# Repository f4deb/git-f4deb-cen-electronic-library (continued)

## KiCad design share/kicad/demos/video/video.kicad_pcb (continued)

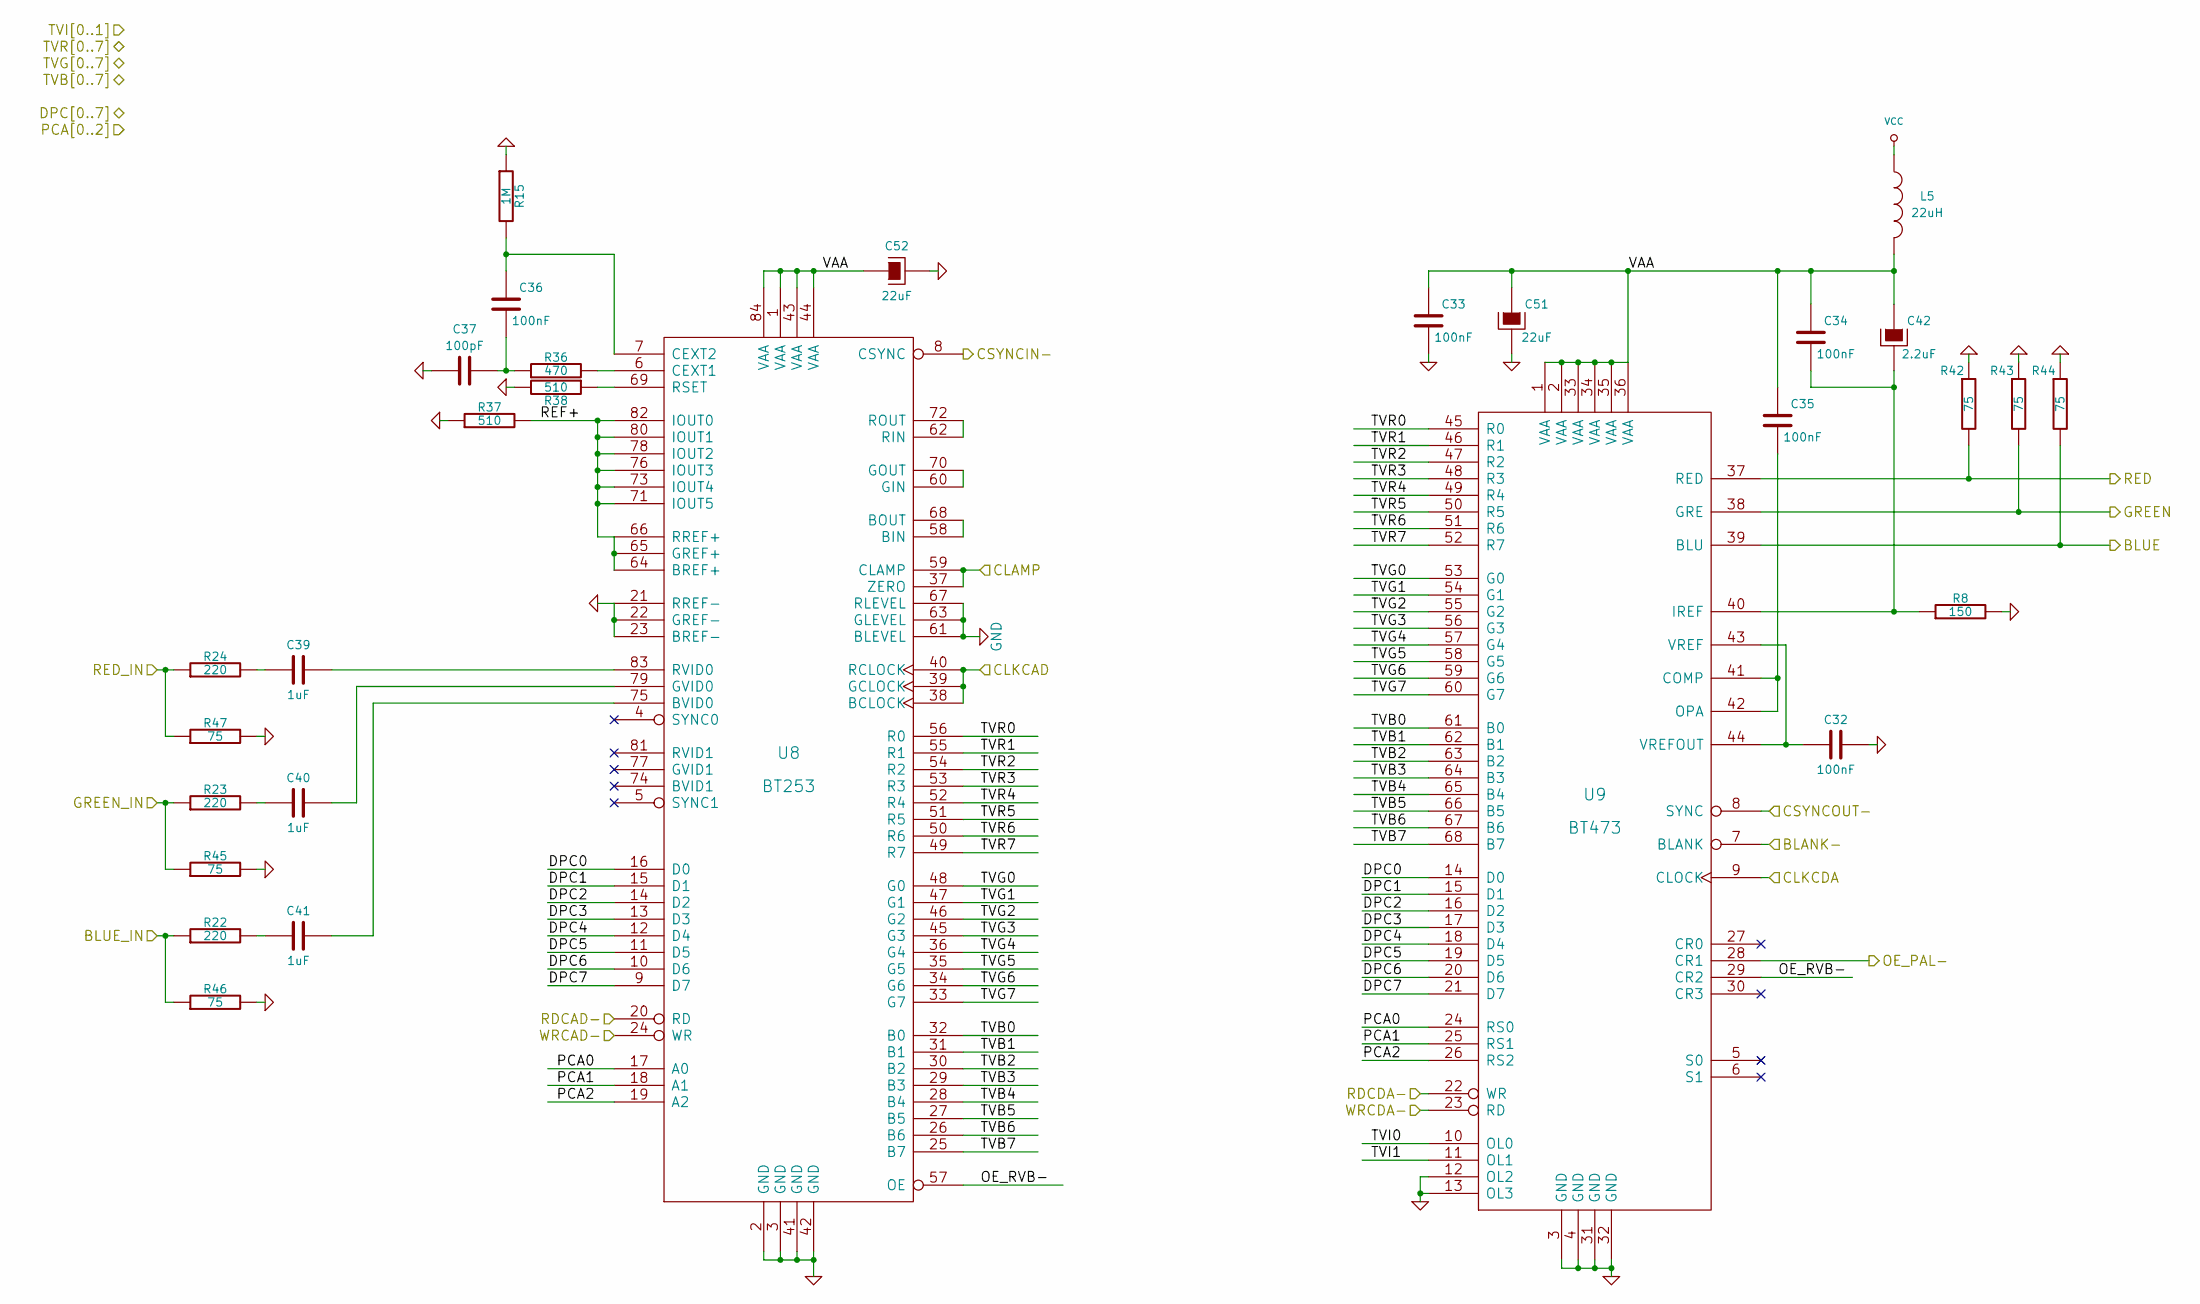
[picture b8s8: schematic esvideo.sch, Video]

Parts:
C32, C33, C34, C35, C36: 100nF; SM1206
C37: 100pF; SM1206
C39, C40, C41: 1uF; SM1210L
C42: 2.2uF; SM1210L
C51: 22uF; SM1210L
C52: 22uF; SM1206
L5: 22uH; SM1812
R8: 150; SM1206
R15: 1M; SM1206
R22, R23, R24: 220; SM1206
R36: 470; SM1206
R37, R38: 510; SM1206
R42, R43, R44, R45, R46, R47: 75; SM1206
U8: BT253; PLCC84
U9: BT473; PLCC68

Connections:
/ESVIDEO-RVB/BLANK-: U9.7 (BLANK); also elsewhere on the board
/ESVIDEO-RVB/BLUE: R44.2, U9.39 (BLU); also elsewhere on the board
/ESVIDEO-RVB/BLUE_IN: R22.1, R46.1; also elsewhere on the board
/ESVIDEO-RVB/CLAMP: U8.37 (ZERO), U8.59 (CLAMP); also elsewhere on the board
/ESVIDEO-RVB/CSYNCIN-: U8.8 (CSYNC); also elsewhere on the board
/ESVIDEO-RVB/DPC0: U8.16 (D0), U9.14 (D0); also elsewhere on the board
/ESVIDEO-RVB/DPC1: U8.15 (D1), U9.15 (D1); also elsewhere on the board
/ESVIDEO-RVB/DPC2: U8.14 (D2), U9.16 (D2); also elsewhere on the board
/ESVIDEO-RVB/DPC3: U8.13 (D3), U9.17 (D3); also elsewhere on the board
/ESVIDEO-RVB/DPC4: U8.12 (D4), U9.18 (D4); also elsewhere on the board
/ESVIDEO-RVB/DPC5: U8.11 (D5), U9.19 (D5); also elsewhere on the board
/ESVIDEO-RVB/DPC6: U8.10 (D6), U9.20 (D6); also elsewhere on the board
/ESVIDEO-RVB/DPC7: U8.9 (D7), U9.21 (D7); also elsewhere on the board
/ESVIDEO-RVB/GREEN: R43.2, U9.38 (GRE); also elsewhere on the board
/ESVIDEO-RVB/GREEN_IN: R23.1, R45.1; also elsewhere on the board
/ESVIDEO-RVB/OE_PAL-: U9.28 (CR1); also elsewhere on the board
/ESVIDEO-RVB/OE_RVB-: U8.57 (OE), U9.29 (CR2)
/ESVIDEO-RVB/PCA0: U8.17 (A0), U9.24 (RS0); also elsewhere on the board
/ESVIDEO-RVB/PCA1: U8.18 (A1), U9.25 (RS1); also elsewhere on the board
/ESVIDEO-RVB/PCA2: U8.19 (A2), U9.26 (RS2); also elsewhere on the board
/ESVIDEO-RVB/RDCAD-: U8.20 (RD); also elsewhere on the board
/ESVIDEO-RVB/RDCDA-: U9.22 (WR); also elsewhere on the board
/ESVIDEO-RVB/RED_IN: R24.1, R47.1; also elsewhere on the board
/ESVIDEO-RVB/REF+: R37.2, U8.64 (BREF+), U8.65 (GREF+), U8.66 (RREF+), U8.71 (IOUT5), U8.73 (IOUT4), U8.76 (IOUT3), U8.78 (IOUT2), U8.80 (IOUT1), U8.82 (IOUT0)
/ESVIDEO-RVB/TVB0: U8.32 (B0), U9.61 (B0); also elsewhere on the board
/ESVIDEO-RVB/TVB1: U8.31 (B1), U9.62 (B1); also elsewhere on the board
/ESVIDEO-RVB/TVB2: U8.30 (B2), U9.63 (B2); also elsewhere on the board
/ESVIDEO-RVB/TVB3: U8.29 (B3), U9.64 (B3); also elsewhere on the board
/ESVIDEO-RVB/TVB4: U8.28 (B4), U9.65 (B4); also elsewhere on the board
/ESVIDEO-RVB/TVB5: U8.27 (B5), U9.66 (B5); also elsewhere on the board
/ESVIDEO-RVB/TVB6: U8.26 (B6), U9.67 (B6); also elsewhere on the board
/ESVIDEO-RVB/TVB7: U8.25 (B7), U9.68 (B7); also elsewhere on the board
/ESVIDEO-RVB/TVG0: U8.48 (G0), U9.53 (G0); also elsewhere on the board
/ESVIDEO-RVB/TVG1: U8.47 (G1), U9.54 (G1); also elsewhere on the board
/ESVIDEO-RVB/TVG2: U8.46 (G2), U9.55 (G2); also elsewhere on the board
/ESVIDEO-RVB/TVG3: U8.45 (G3), U9.56 (G3); also elsewhere on the board
/ESVIDEO-RVB/TVG4: U8.36 (G4), U9.57 (G4); also elsewhere on the board
/ESVIDEO-RVB/TVG5: U8.35 (G5), U9.58 (G5); also elsewhere on the board
/ESVIDEO-RVB/TVG6: U8.34 (G6), U9.59 (G6); also elsewhere on the board
/ESVIDEO-RVB/TVG7: U8.33 (G7), U9.60 (G7); also elsewhere on the board
/ESVIDEO-RVB/TVI0: U9.10 (OL0); also elsewhere on the board
/ESVIDEO-RVB/TVI1: U9.11 (OL1); also elsewhere on the board
/ESVIDEO-RVB/TVR0: U8.56 (R0), U9.45 (R0); also elsewhere on the board
/ESVIDEO-RVB/TVR1: U8.55 (R1), U9.46 (R1); also elsewhere on the board
/ESVIDEO-RVB/TVR2: U8.54 (R2), U9.47 (R2); also elsewhere on the board
/ESVIDEO-RVB/TVR3: U8.53 (R3), U9.48 (R3); also elsewhere on the board
/ESVIDEO-RVB/TVR4: U8.52 (R4), U9.49 (R4); also elsewhere on the board
/ESVIDEO-RVB/TVR5: U8.51 (R5), U9.50 (R5); also elsewhere on the board
/ESVIDEO-RVB/TVR6: U8.50 (R6), U9.51 (R6); also elsewhere on the board
/ESVIDEO-RVB/TVR7: U8.49 (R7), U9.52 (R7); also elsewhere on the board
/ESVIDEO-RVB/VAA: C33.1, C34.1, C35.1, C42.1, C51.1, C52.1, L5.2, U8.1 (VAA), U8.43 (VAA), U8.44 (VAA), U8.84 (VAA), U9.1 (VAA), U9.2 (VAA), U9.33 (VAA), U9.34 (VAA), U9.35 (VAA), U9.36 (VAA)
/ESVIDEO-RVB/WRCAD-: U8.24 (WR); also elsewhere on the board
/ESVIDEO-RVB/WRCDA-: U9.23 (RD); also elsewhere on the board
/graphic/CADCLK: U8.38 (BCLOCK), U8.39 (GCLOCK), U8.40 (RCLOCK); also elsewhere on the board
/graphic/CDACLK: U9.9 (CLOCK); also elsewhere on the board
/graphic/CSYNC-OUT: U9.8 (SYNC); also elsewhere on the board
/modul/BLEU: R42.2, U9.37 (RED); also elsewhere on the board
GND: C32.1, C33.2, C37.1, C51.2, C52.2, R8.2, R15.1, R37.1, R38.2, R42.1, R43.1, R44.1, R45.2, R46.2, R47.2, U8.2 (GND), U8.3 (GND), U8.21 (RREF-), U8.22 (GREF-), U8.23 (BREF-), U8.41 (GND), U8.42 (GND), U8.61 (BLEVEL), U8.63 (GLEVEL), U8.67 (RLEVEL), U9.3 (GND), U9.4 (GND), U9.12 (OL2), U9.13 (OL3), U9.31 (GND), U9.32 (GND); also elsewhere on the board
unnamed: C32.2, U9.43 (VREF), U9.44 (VREFOUT)
unnamed: C34.2, C42.2, R8.1, U9.40 (IREF)
unnamed: C35.2, U9.41 (COMP), U9.42 (OPA)
unnamed: C36.1, R15.2, U8.7 (CEXT2)
unnamed: C36.2, C37.2, R36.1
unnamed: C39.1, U8.83 (RVID0)
unnamed: C39.2, R24.2
unnamed: C40.1, U8.79 (GVID0)
unnamed: C40.2, R23.2
unnamed: C41.1, U8.75 (BVID0)
unnamed: C41.2, R22.2
unnamed: R36.2, U8.6 (CEXT1)
unnamed: R38.1, U8.69 (RSET)
unnamed: U8.58 (BIN), U8.68 (BOUT)
unnamed: U8.60 (GIN), U8.70 (GOUT)
unnamed: U8.62 (RIN), U8.72 (ROUT)
VCC: L5.1; also elsewhere on the board

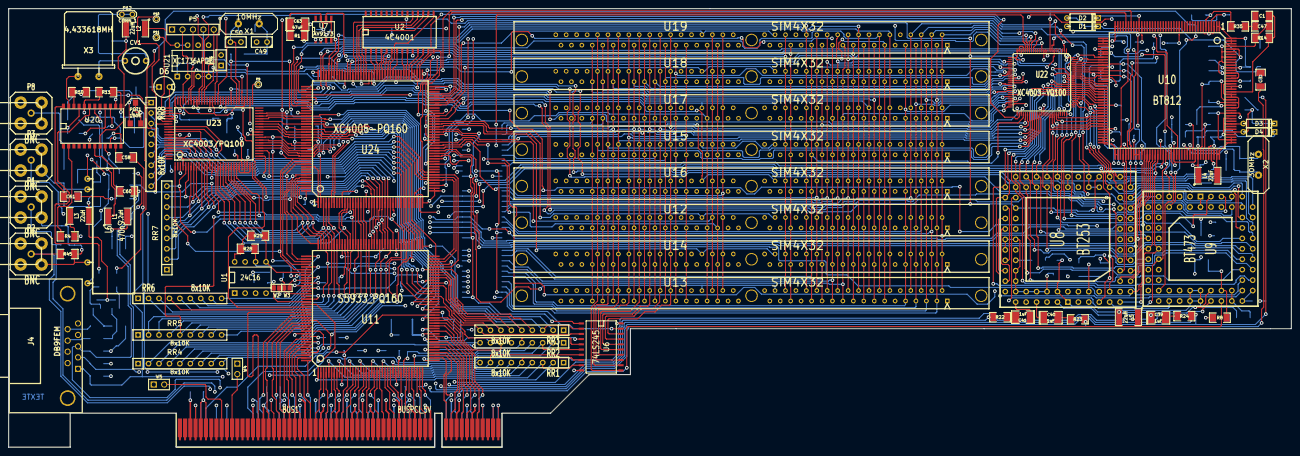
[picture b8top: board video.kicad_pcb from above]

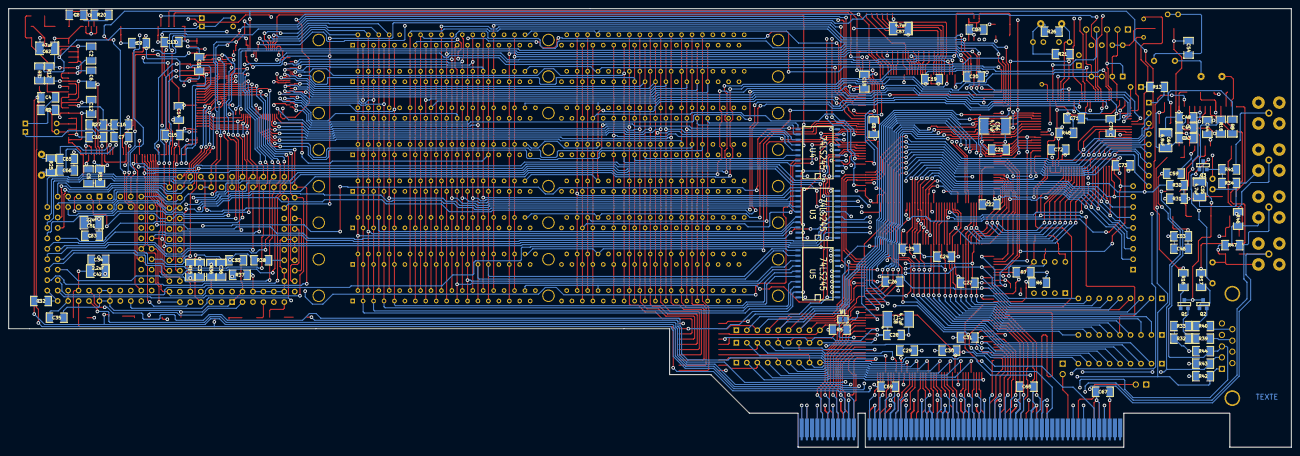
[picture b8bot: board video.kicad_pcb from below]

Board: 4 copper layers, 312.0 x 106.7 mm, 189 parts (103 on the bottom side), 371 nets.

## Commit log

2012-08-18 Creation du depot et ajout de la librairie en cours
2012-08-18 add of readme.md
2013-06-04 Ajout SBL 2D 3D
2013-06-09 Ajout composant 3D
2013-06-16 SOT220 5 broches+xtal quad
2013-06-24 MAJ3D
2013-07-03 LED CMS 1W 3D 2D
2013-08-03 AJOUT 3D ECA3
2014-07-11 Ajout composant pour IOIO Board
2014-07-13 MAJ RJ12_CMS Wings+LIB kicad
2014-07-18 ADD 3D COMPONENTS
2014-07-19 ADD CAPA 10F
2014-09-29 ADD LM75ADP+24C16
2015-07-15 ADD MOD + 3D
2015-07-27 ADD CRYSTAL + PIN STRIPP
2015-08-02 New library
2015-08-06 add PG-TO220-7-4
2015-08-20 ADD crystal MDX75104
2015-12-20 Update for Beacon_Main_Board
2017-07-10 Ajout fichier 3D dans KISYS3DMOD
